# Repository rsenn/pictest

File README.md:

https://github.com/broedsels/PING2550
https://github.com/Apress/programming-pic-microcontrollers-w-xc8

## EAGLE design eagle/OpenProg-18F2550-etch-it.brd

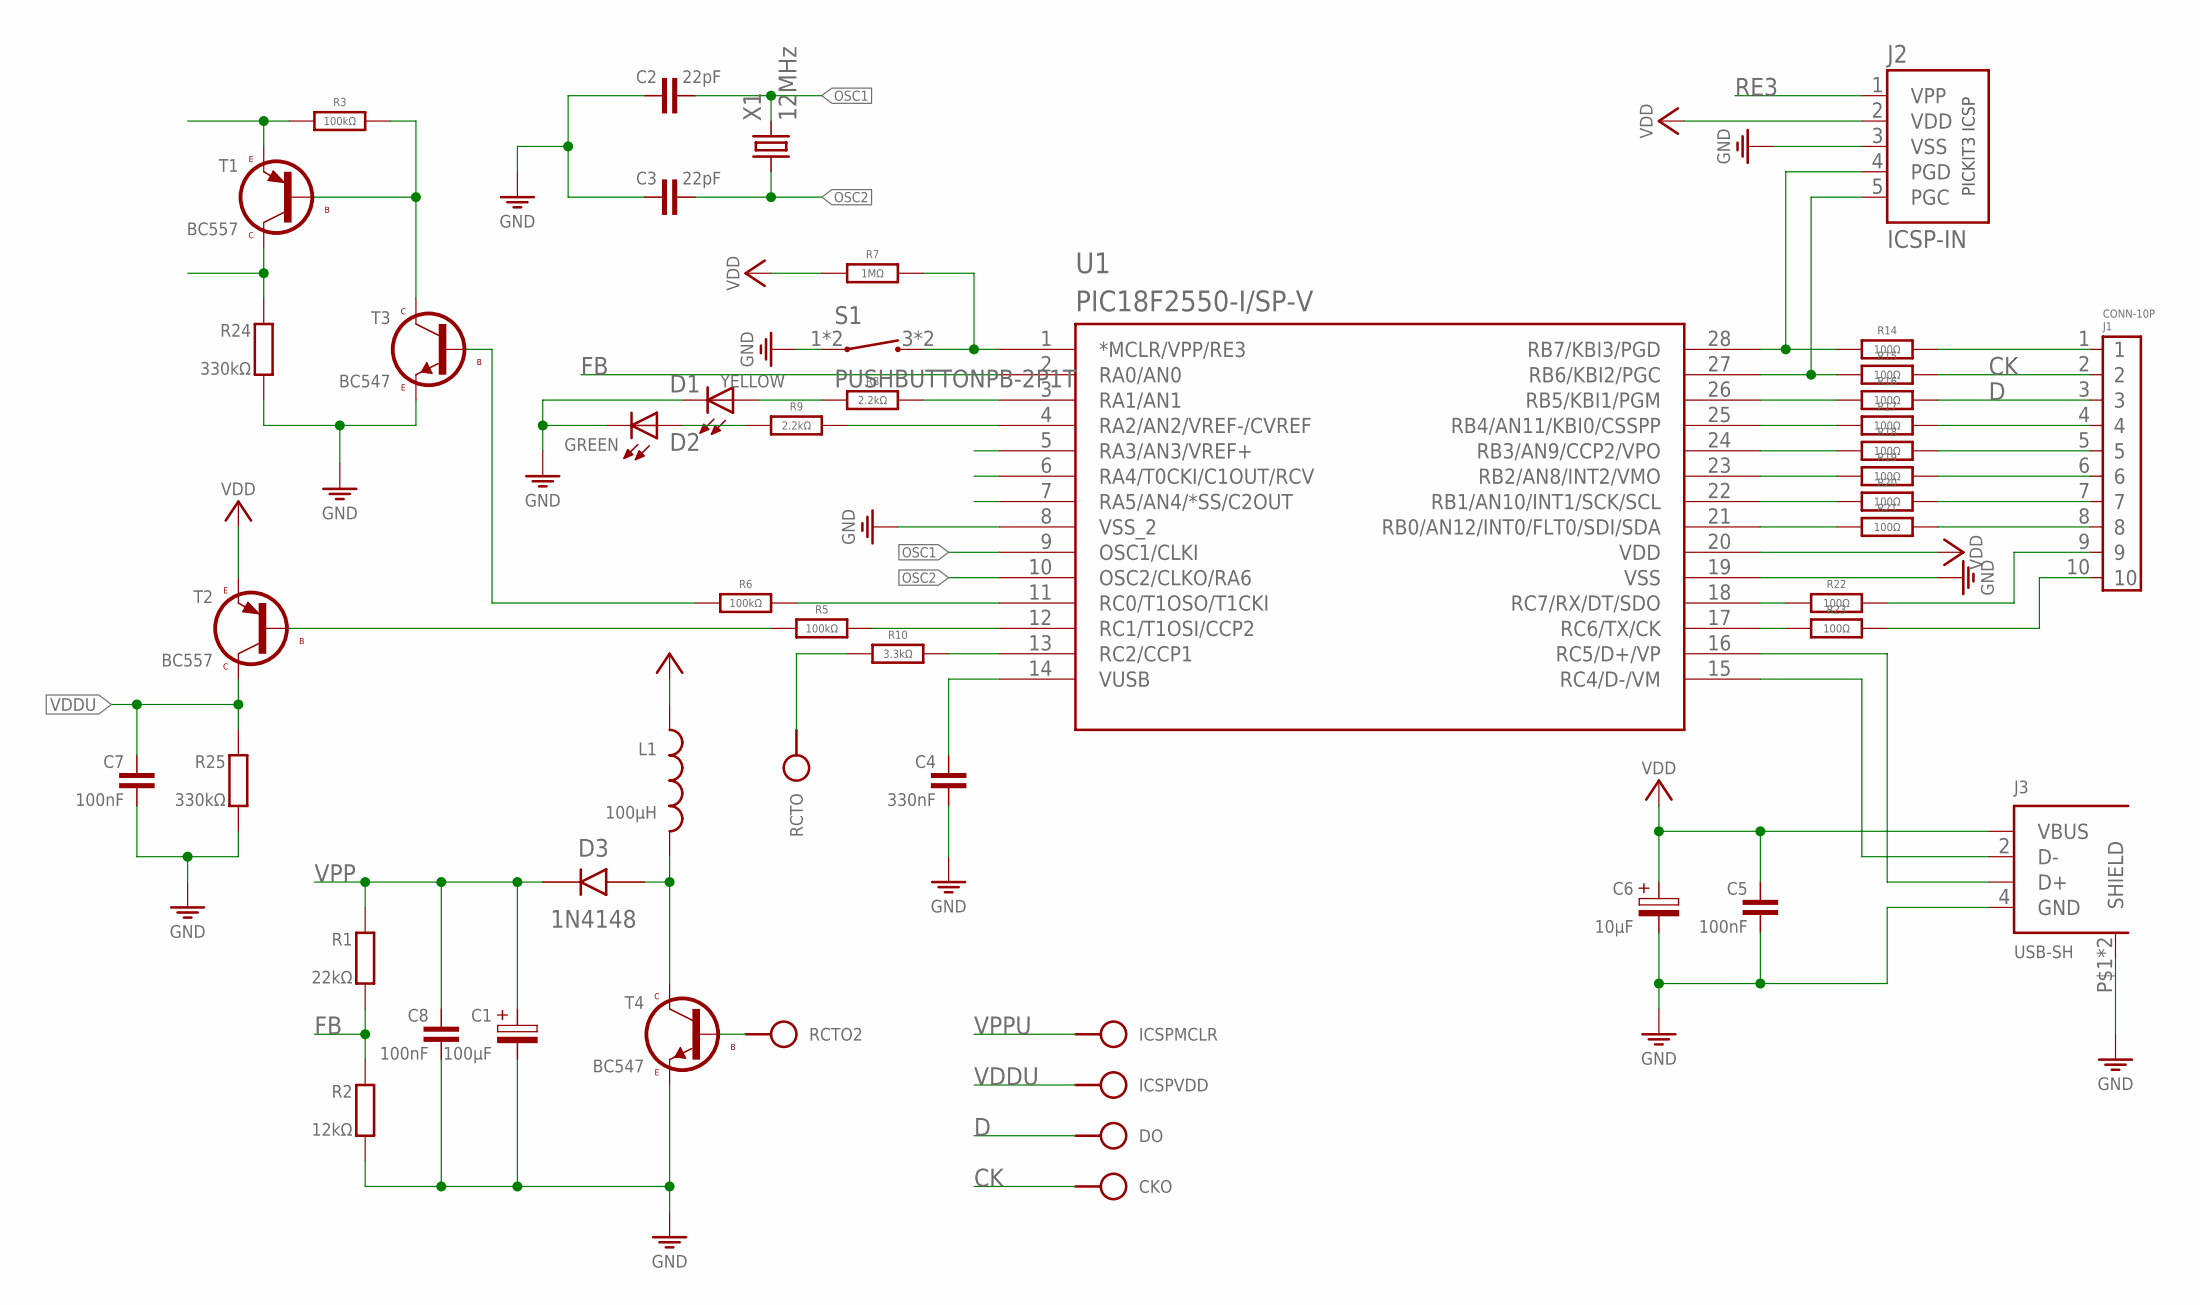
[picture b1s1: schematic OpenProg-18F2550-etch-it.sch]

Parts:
C1: 100μF; E2,5-5/V
C2, C3: 22pF; C025-015X024
C4: 330nF; C050-030X075
C5, C8: 100nF; C025-015X024
C6: 10μF; E2,5-5
C7: 100nF; C050-020X036
CKO: HPORT; SPAD
D1: YELLOW; LED_3MM
D2: GREEN; LED_3MM
D3: 1N4148; DO34-7
DO: HPORT; SPAD
ICSPMCLR: HPORT; SPAD
ICSPVDD: HPORT; SPAD
J1: CONN-10P
J2: ICSP-IN; PIC-PK3
J3: USB-SH; USB-B-PRINT
L1: 100µH; L-03/10V
R1: 22kΩ; 0204/10-V
R2: 12kΩ; 0204/10-V
R3: 100kΩ; 0204/2
R5, R6: 100kΩ; 0204/10
R7: 1MΩ; 0204/10-V
R8, R9: 2.2kΩ; 0204/10
R10: 3.3kΩ; 0204/10
R14, R15, R16, R17, R18, R19, R20, R21, R22, R23: 100Ω; 0204/10
R24, R25: 330kΩ; 0204/10-V
RCTO, RCTO2: HPORT; SPAD
S1: PUSHBUTTONPB-2P1T; PB-2P1T
T1, T2: BC557; TO92-CBE
T3, T4: BC547; TO92
U1: PIC18F2550-I/SP-V; DIL28-3/V
X1: 12MHz; HC49

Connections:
CK: CKO.1, J1.2, R15.2
D: DO.1, J1.3, R16.2
FB: R1.2 (1), R2.1 (2), U1.2 (RA0/AN0)
GND: C1.-, C2.1, C3.1, C4.2, C5.2, C6.-, C7.2, C8.2, D1.K (C), D2.K (C), J2.3 (VSS), J3.4 (GND), J3.P$1 (SHIELD), J3.P$2 (SHIELD), R2.2 (1), R24.2 (1), R25.2 (1), S1.1, S1.2 (1), T3.3 (E), T4.3 (E), U1.8 (VSS_2), U1.19 (VSS)
unnamed: R5.1, T2.2 (B)
unnamed: D3.A, L1.2, T4.1 (C)
unnamed: R10.1, RCTO.1
unnamed: R3.2, T1.2 (B), T3.1 (C)
unnamed: J2.4 (PGD), R14.1, U1.28 (RB7/KBI3/PGD)
unnamed: J2.5 (PGC), R15.1, U1.27 (RB6/KBI2/PGC)
unnamed: R16.1, U1.26 (RB5/KBI1/PGM)
unnamed: R17.1, U1.25 (RB4/AN11/KBI0/CSSPP)
unnamed: R18.1, U1.24 (RB3/AN9/CCP2/VPO)
unnamed: R19.1, U1.23 (RB2/AN8/INT2/VMO)
unnamed: R20.1, U1.22 (RB1/AN10/INT1/SCK/SCL)
unnamed: R21.1, U1.21 (RB0/AN12/INT0/FLT0/SDI/SDA)
unnamed: J1.1, R14.2
unnamed: J1.4, R17.2
unnamed: J1.5, R18.2
unnamed: J1.6, R19.2
unnamed: J1.7, R20.2
unnamed: R22.1, U1.18 (RC7/RX/DT/SDO)
unnamed: R23.1, U1.17 (RC6/TX/CK)
unnamed: J1.9, R22.2
unnamed: J1.10, R23.2
unnamed: J3.3 (D+), U1.16 (RC5/D+/VP)
unnamed: C4.1, U1.14 (VUSB)
unnamed: D1.A, R8.1
unnamed: D2.A, R9.1
OSC1: C2.2, U1.9 (OSC1/CLKI), X1.2
OSC2: C3.2, U1.10 (OSC2/CLKO/RA6), X1.1
RA1: R8.2, U1.3 (RA1/AN1)
RA2: R9.2, U1.4 (RA2/AN2/VREF-/CVREF)
RC0: R6.2, U1.11 (RC0/T1OSO/T1CKI)
RC1: R5.2, U1.12 (RC1/T1OSI/CCP2)
RC2: R10.2, U1.13 (RC2/CCP1)
RE3: J2.1 (VPP), R7.2, S1.3 (2), S1.4 (2), U1.1 (*MCLR/VPP/RE3)
VCC: C5.1, C6.+, J2.2 (VDD), J3.1 (VBUS), L1.1, R7.1, T2.3 (E), U1.20 (VDD)
VDD1: J1.8, R21.2
VDD3: J3.2 (D-), U1.15 (RC4/D-/VM)
VDDU: C7.1, ICSPVDD.1, R25.1 (2), T2.1 (C)
VPP: C1.+, C8.1, D3.C, R1.1 (2), R3.1, T1.3 (E)
VPPCTL: R6.1, T3.2 (B)
VPPU: ICSPMCLR.1, R24.1 (2), T1.1 (C)
VREGCTL: RCTO2.1, T4.2 (B)

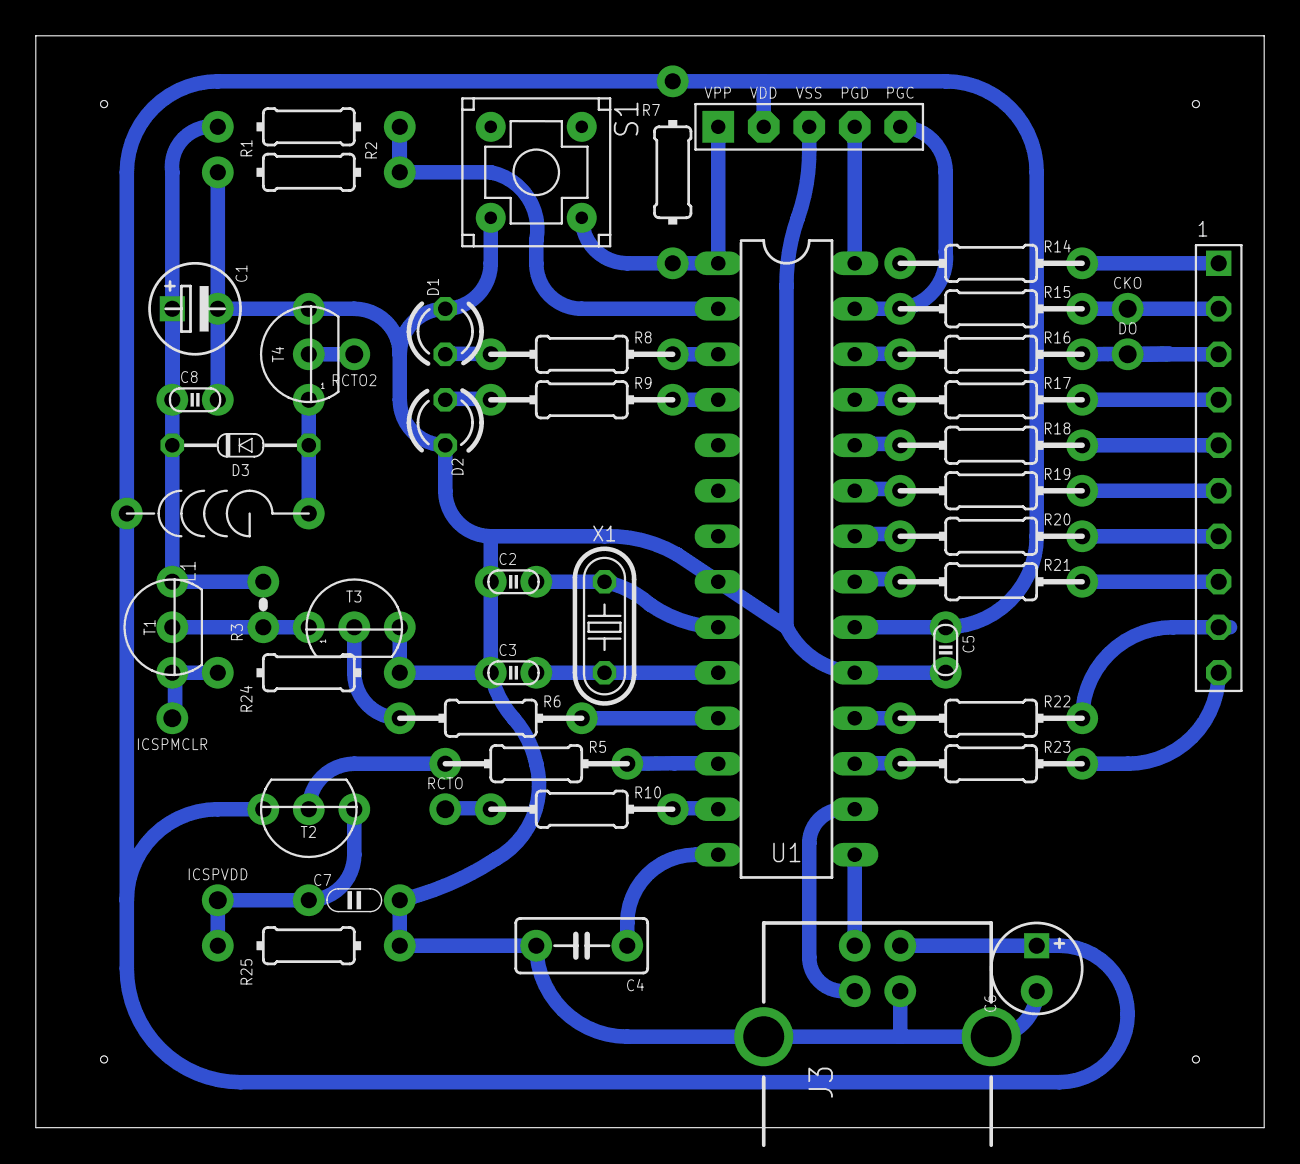
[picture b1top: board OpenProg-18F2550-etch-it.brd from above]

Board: 2 copper layers, 68.6 x 61.0 mm, 49 parts (0 on the bottom side), 45 nets.

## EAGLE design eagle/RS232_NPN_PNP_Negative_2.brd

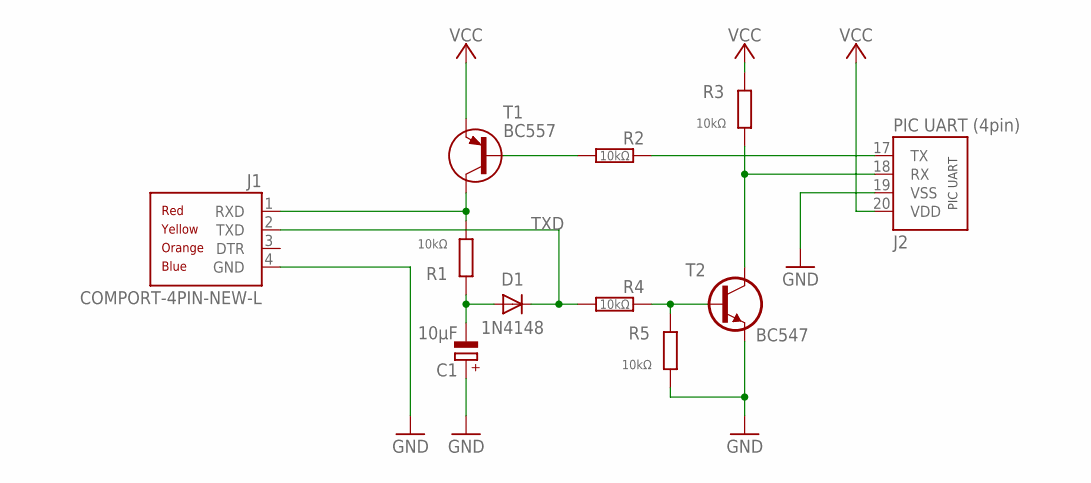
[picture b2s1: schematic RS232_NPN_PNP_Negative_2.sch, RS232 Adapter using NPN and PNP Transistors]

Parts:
C1: 10μF; E2,5-3/V
D1: 1N4148; DO34-5
J1: COMPORT-4PIN-NEW-L; RS232-4PIN-NEW-L
J2: PIC UART (4pin); PIC-UART
R1, R4, R5: 10kΩ; 0202/7
R2: 10kΩ; 0202/10-V
R3: 10kΩ; 0202/7-V
T1: BC557; TO92-CBE
T2: BC547; TO92-CBE

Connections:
-12V: C1.-, D1.A, R1.1
GND: C1.+, J1.4 (GND), J2.19 (VSS), R5.2, T2.E
unnamed: R2.2, T1.B
unnamed: R4.1, R5.1, T2.B
RX: J2.18 (RX), R3.1, T2.C
RXD: J1.1 (RXD), R1.2, T1.C
TX: J2.17 (TX), R2.1
TXD: D1.C, J1.2 (TXD), R4.2
VCC: J2.20 (VDD), R3.2, T1.E

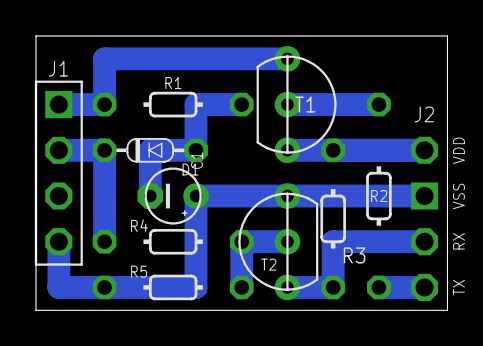
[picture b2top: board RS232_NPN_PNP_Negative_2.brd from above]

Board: 2 copper layers, 22.9 x 15.2 mm, 11 parts (0 on the bottom side), 9 nets.

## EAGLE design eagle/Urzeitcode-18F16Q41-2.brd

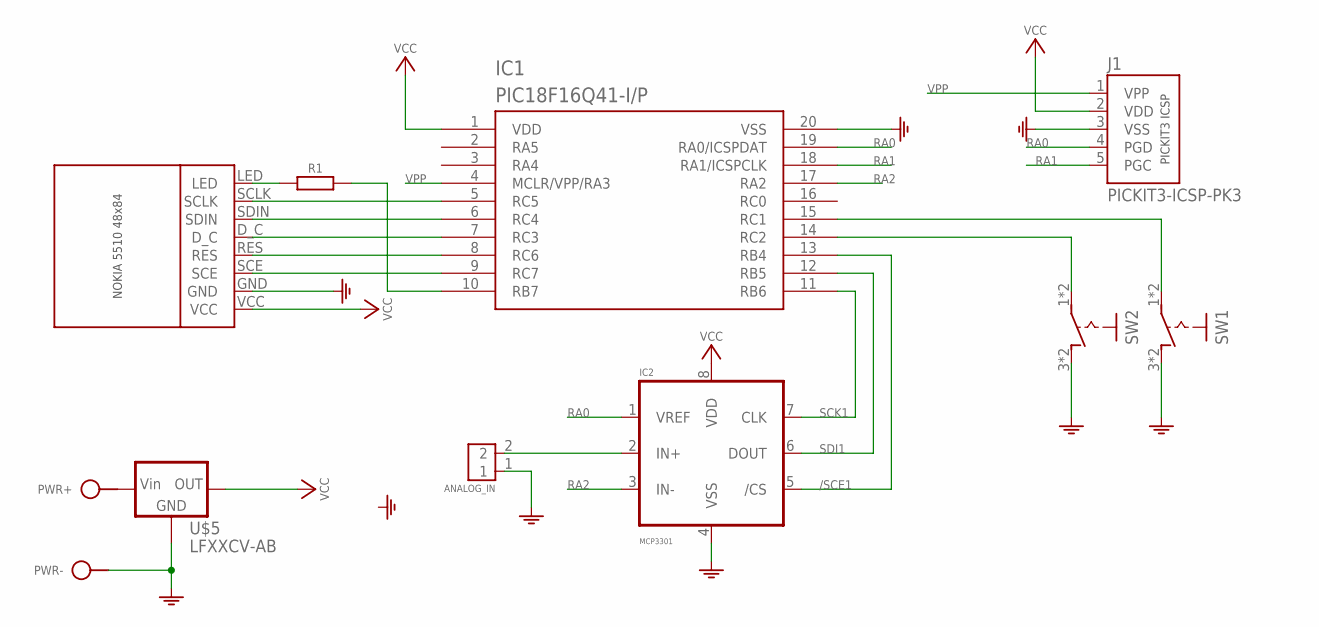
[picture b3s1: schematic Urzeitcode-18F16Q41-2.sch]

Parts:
ANALOG_IN: CONN-2P2P/H; CONN-2P
IC1: PIC18F16Q41-I/P; DIL20-3/V
IC2: MCP3301; DIL08
J1: PICKIT3-ICSP-PK3; PIC-PK3
PWR: SPAD+--+; SPAD-+
R1: R-H0204/15-V; 0204/15-V
SW1, SW2: PB-1P-1T2P1T; PB-2P1T
U$2: NOKIA-5510-48X84-MODULE; MOD-LCD5110
U$5: LFXXCV-AB; TO220AB

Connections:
/SCE1: IC1.13 (RB4), IC2.5 (/CS)
GND: ANALOG_IN.1, IC1.20 (VSS), IC2.4 (VSS), J1.3 (VSS), PWR.1, SW1.3 (S), SW1.4 (S), SW2.3 (S), SW2.4 (S), U$2.GND, U$5.2 (GND)
unnamed: PWR.2, U$5.1 (VIN)
unnamed: ANALOG_IN.2, IC2.2 (IN+)
unnamed: R1.1, U$2.LED
unnamed: IC1.14 (RC2), SW2.1, SW2.2
unnamed: IC1.15 (RC1), SW1.1, SW1.2
RA0: IC1.19 (RA0/ICSPDAT), IC2.1 (VREF), J1.4 (PGD)
RA1: IC1.18 (RA1/ICSPCLK), J1.5 (PGC)
RA2: IC1.17 (RA2), IC2.3 (IN-)
RB7: IC1.10 (RB7), R1.2
RC3: IC1.7 (RC3), U$2.D_C
RC4: IC1.6 (RC4), U$2.SDIN
RC5: IC1.5 (RC5), U$2.SCLK
RC6: IC1.8 (RC6), U$2.RES
RC7: IC1.9 (RC7), U$2.SCE
SCK1: IC1.11 (RB6), IC2.7 (CLK)
SDI1: IC1.12 (RB5), IC2.6 (DOUT)
VCC: IC1.1 (VDD), IC2.8 (VDD), J1.2 (VDD), U$2.VCC, U$5.3 (VOUT)
VPP: IC1.4 (MCLR/VPP/RA3), J1.1 (VPP)

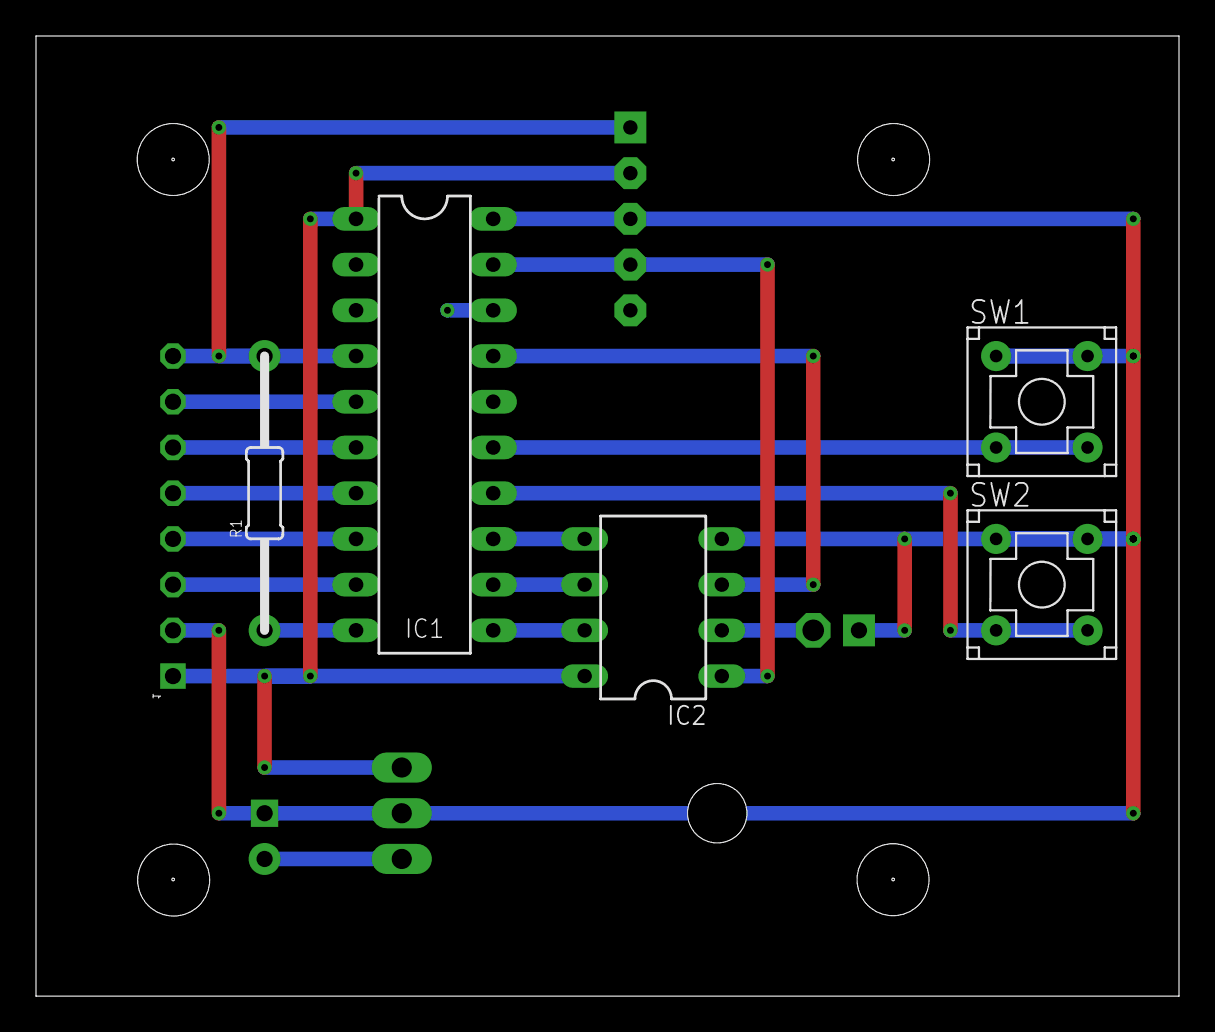
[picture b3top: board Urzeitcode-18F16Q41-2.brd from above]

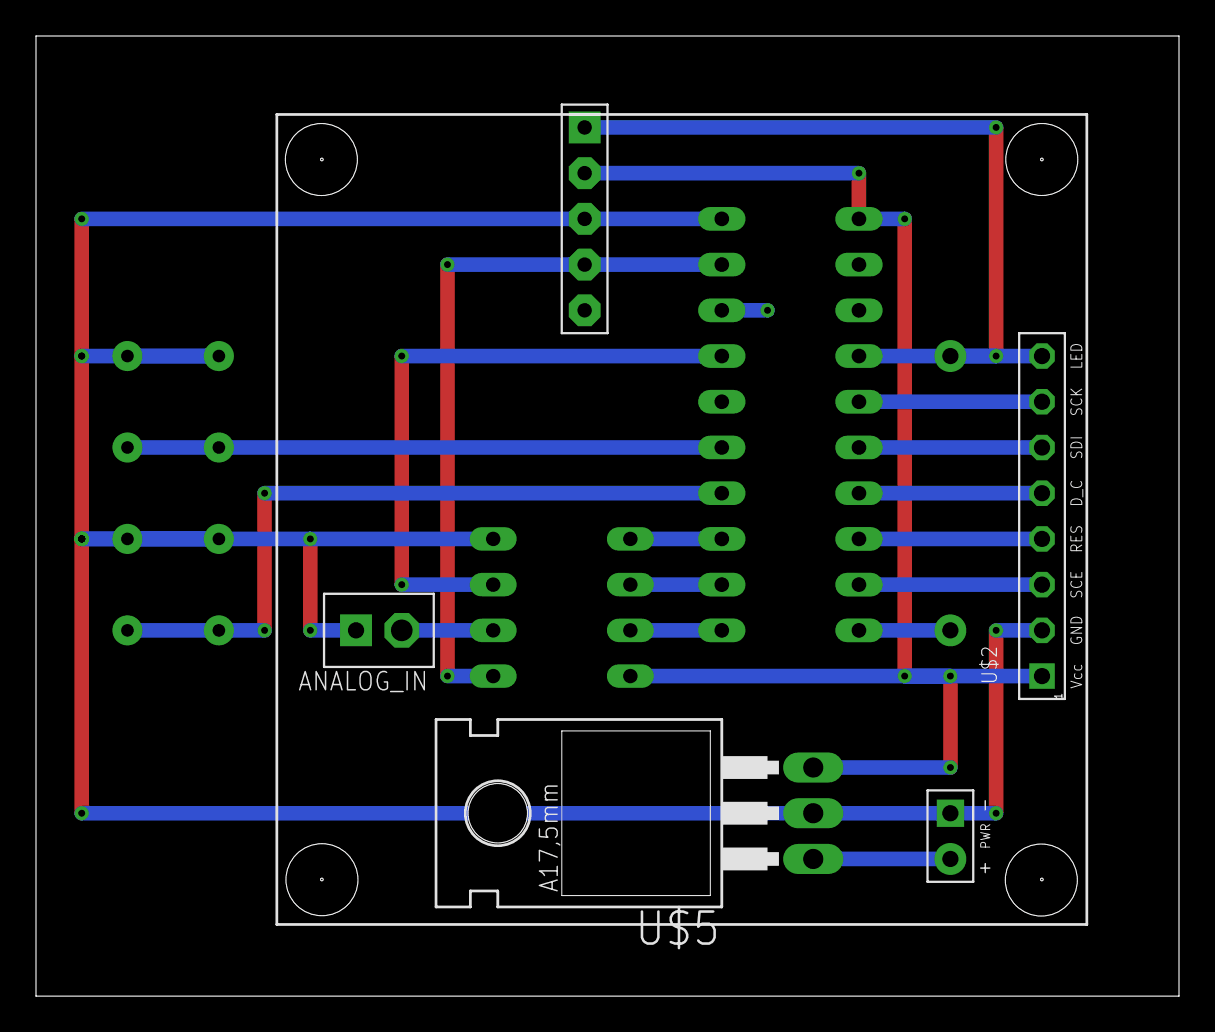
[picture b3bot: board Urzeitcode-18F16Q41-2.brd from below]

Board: 2 copper layers, 63.5 x 53.3 mm, 10 parts (4 on the bottom side), 20 nets.

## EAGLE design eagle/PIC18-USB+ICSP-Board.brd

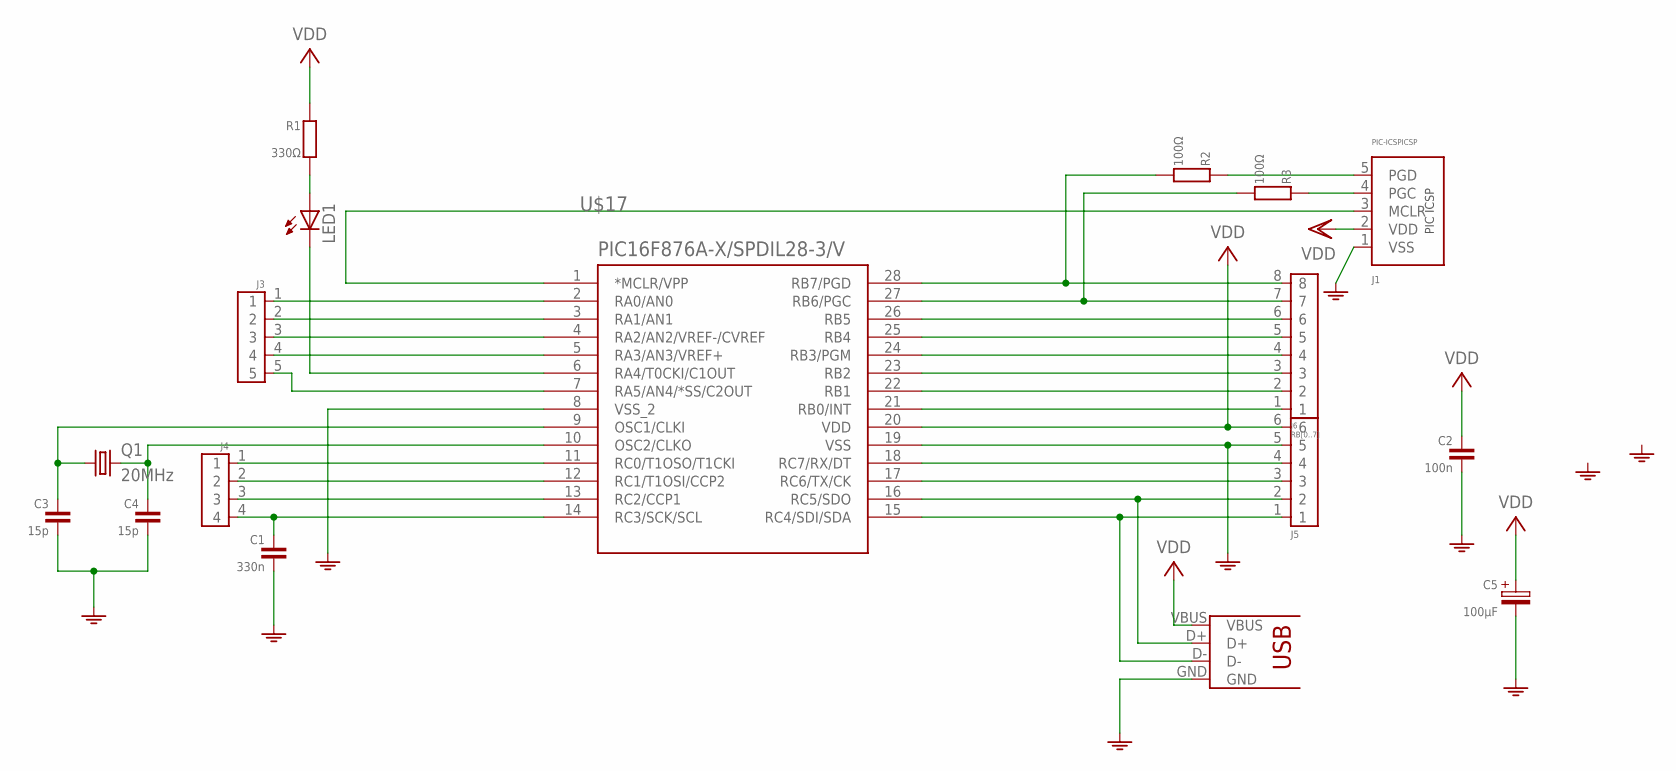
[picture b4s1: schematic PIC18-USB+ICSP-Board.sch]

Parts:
C1: 330n; C050-030X075
C2: 100n; C025-015X024
C3, C4: 15p; C025-015X024
C5: 100μF; E2,5-5
J1: PIC-ICSPICSP; PIC-ICSP
J2: USB-PRINT; USB-B-PRINT
J3: RA[0..4]; CONN-5P
J4: RC[0..3]; CONN-4P
J5: PWR+SCI+USB; CONN-6P
J6: RB[0..7]; CONN-8P
LED1: LED5MM
Q1: 20MHz; HC49
R1: 330Ω; 0204/10
R2, R3: 100Ω; 0204/7-V
U$17: PIC16F876A-X/SPDIL28-3/V; DIL28-3/V

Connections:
/MCLR: J1.3 (MCLR), U$17.1 (*MCLR/VPP)
GND: C1.2, C2.2, C3.2, C4.2, C5.-, J1.1 (VSS), J2.GND, J5.5, U$17.8 (VSS_2), U$17.19 (VSS)
unnamed: C1.1, J4.4, U$17.14 (RC3/SCK/SCL)
unnamed: J2.D+, J5.2, U$17.16 (RC5/SDO)
unnamed: J2.D-, J5.1, U$17.15 (RC4/SDI/SDA)
unnamed: LED1.A, R1.2 (1)
unnamed: J3.5, U$17.7 (RA5/AN4/*SS/C2OUT)
unnamed: C3.1, Q1.1, U$17.9 (OSC1/CLKI)
unnamed: C4.1, Q1.2, U$17.10 (OSC2/CLKO)
unnamed: J6.6, U$17.26 (RB5)
unnamed: J6.5, U$17.25 (RB4)
unnamed: J6.4, U$17.24 (RB3/PGM)
unnamed: J6.3, U$17.23 (RB2)
unnamed: J6.2, U$17.22 (RB1)
unnamed: J6.1, U$17.21 (RB0/INT)
unnamed: J3.1, U$17.2 (RA0/AN0)
unnamed: J5.4, U$17.18 (RC7/RX/DT)
unnamed: J5.3, U$17.17 (RC6/TX/CK)
unnamed: J3.2, U$17.3 (RA1/AN1)
unnamed: J3.3, U$17.4 (RA2/AN2/VREF-/CVREF)
unnamed: J3.4, U$17.5 (RA3/AN3/VREF+)
unnamed: LED1.K (C), U$17.6 (RA4/T0CKI/C1OUT)
unnamed: J4.1, U$17.11 (RC0/T1OSO/T1CKI)
unnamed: J4.2, U$17.12 (RC1/T1OSI/CCP2)
unnamed: J4.3, U$17.13 (RC2/CCP1)
unnamed: J1.5 (PGD), R2.1 (2)
unnamed: J1.4 (PGC), R3.1 (2)
PGC: J6.7, R3.2 (1), U$17.27 (RB6/PGC)
PGD: J6.8, R2.2 (1), U$17.28 (RB7/PGD)
VDD: C2.1, C5.+, J1.2 (VDD), J2.VBUS, J5.6, R1.1 (2), U$17.20 (VDD)

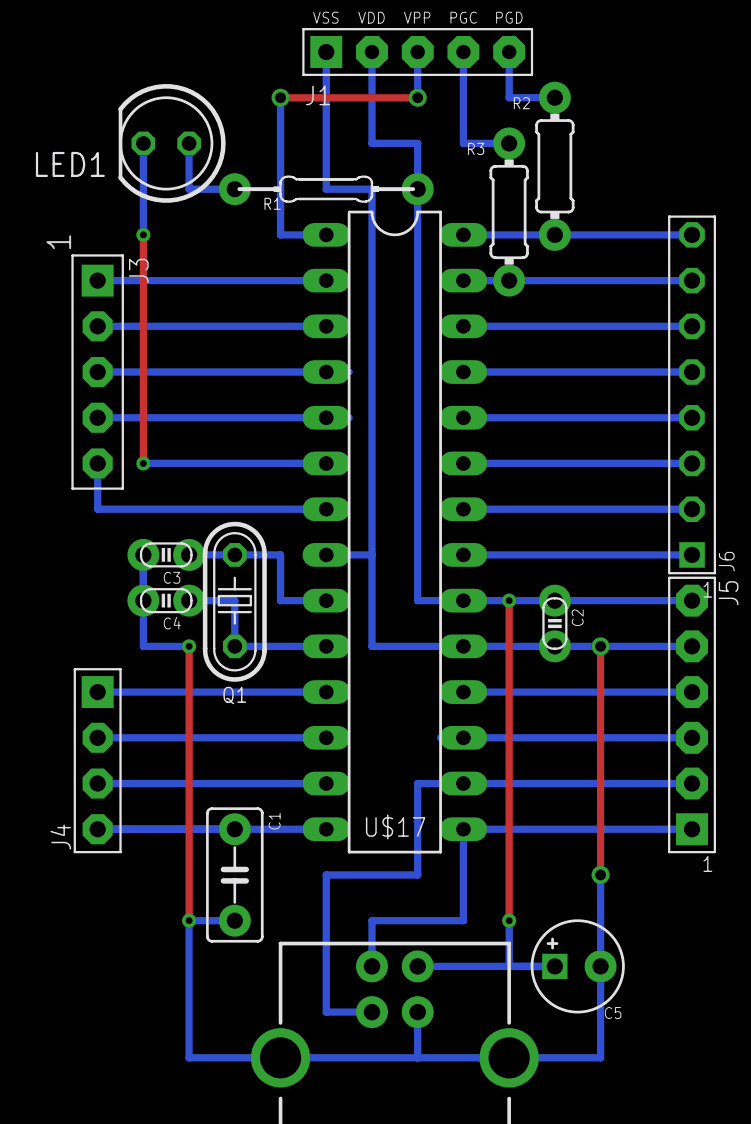
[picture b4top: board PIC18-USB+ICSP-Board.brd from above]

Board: 2 copper layers, 17 parts (0 on the bottom side), 30 nets.

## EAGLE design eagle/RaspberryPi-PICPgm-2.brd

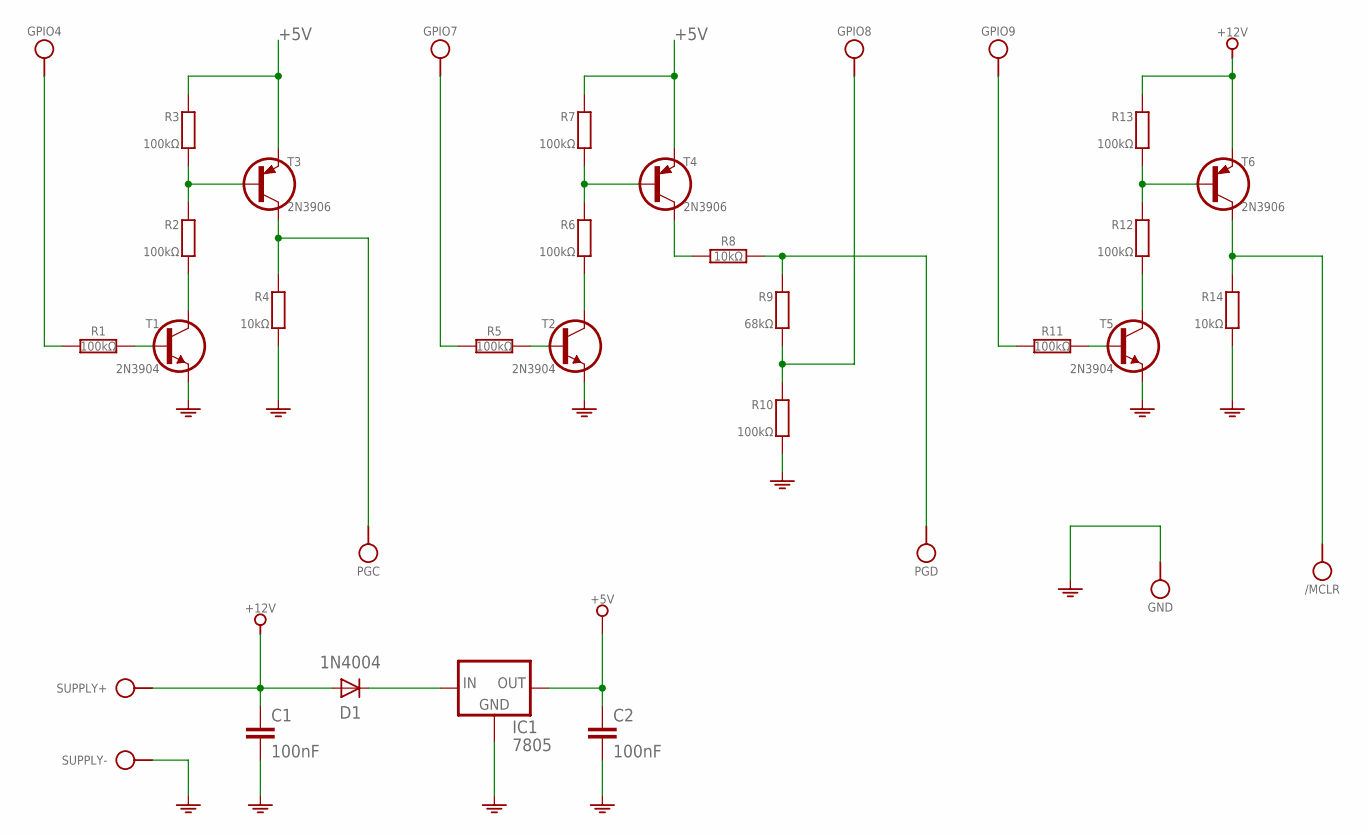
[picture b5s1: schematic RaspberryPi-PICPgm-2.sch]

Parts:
/MCLR: VPORT; SPAD
C1, C2: 100nF; C050-025X075
D1: 1N4004; DO41-10
GND: VPORT; SPAD
GPIO4, GPIO7, GPIO8, GPIO9: VPORT; SPAD
IC1: 7805; TO220
PGC: VPORT; SPAD
PGD: VPORT; SPAD
R1, R5, R11: 100kΩ; 0204/10
R2, R3, R6, R7, R10, R12, R13: 100kΩ; 0204/10-V
R4, R14: 10kΩ; 0204/10-V
R8: 10kΩ; 0204/10
R9: 68kΩ; 0204/10-V
SUPPLY: SPAD+--+; SPAD-+
T1, T2, T5: 2N3904; TO92-EBC
T3, T4, T6: 2N3906; TO92-EBC

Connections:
+5V: C2.1, IC1.3 (OUT), R3.1 (2), R7.1 (2), T3.E, T4.E
+12V: C1.1, D1.A, R13.1 (2), SUPPLY.2, T6.E
GND: C1.2, C2.2, GND.1, IC1.2 (GND), R4.2 (1), R10.2 (1), R14.2 (1), SUPPLY.1, T1.E, T2.E, T5.E
unnamed: GPIO4.1, R1.1
unnamed: R1.2, T1.B
unnamed: R2.2 (1), T1.C
unnamed: R2.1 (2), R3.2 (1), T3.B
unnamed: PGC.1, R4.1 (2), T3.C
unnamed: GPIO7.1, R5.1
unnamed: R5.2, T2.B
unnamed: R6.2 (1), T2.C
unnamed: R6.1 (2), R7.2 (1), T4.B
unnamed: R8.1, T4.C
unnamed: PGD.1, R8.2, R9.1 (2)
unnamed: GPIO8.1, R9.2 (1), R10.1 (2)
unnamed: GPIO9.1, R11.1
unnamed: R11.2, T5.B
unnamed: R12.2 (1), T5.C
unnamed: R12.1 (2), R13.2 (1), T6.B
unnamed: /MCLR.1, R14.1 (2), T6.C
unnamed: D1.C, IC1.1 (IN)

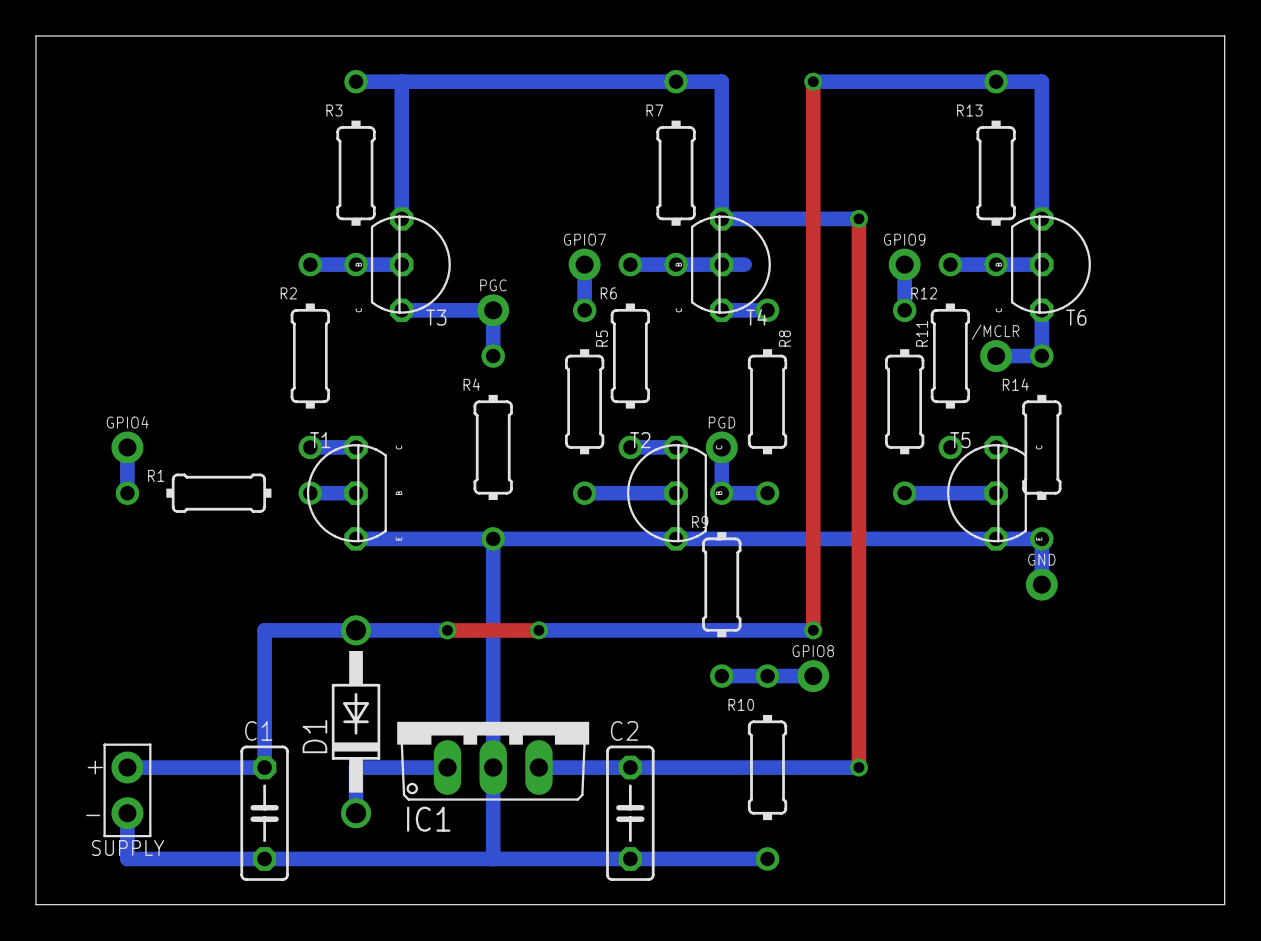
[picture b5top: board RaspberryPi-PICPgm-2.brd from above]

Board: 2 copper layers, 66.0 x 48.3 mm, 33 parts (0 on the bottom side), 21 nets.

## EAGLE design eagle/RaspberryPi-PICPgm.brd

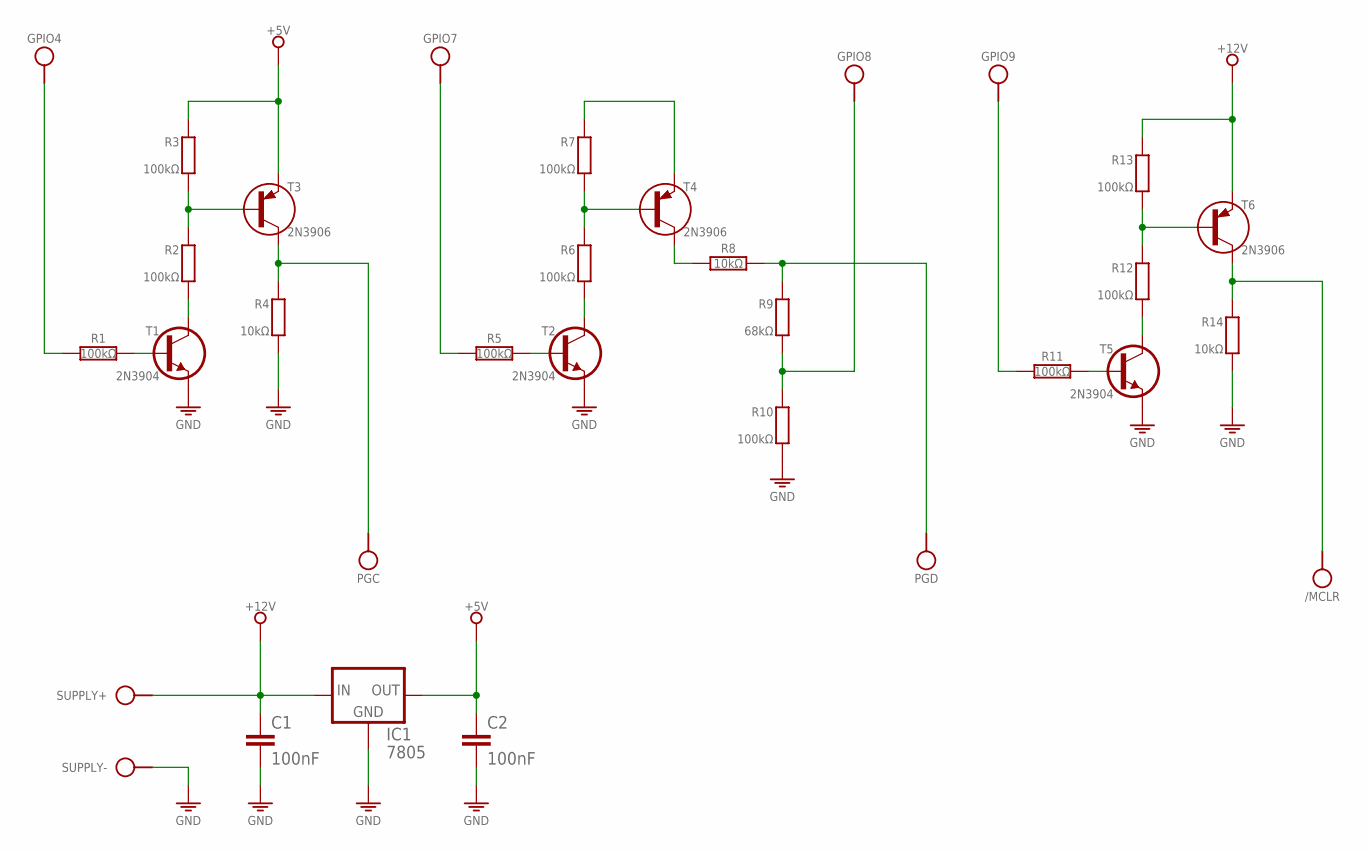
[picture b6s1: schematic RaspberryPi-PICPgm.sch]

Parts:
/MCLR: VPORT; SPAD
C1, C2: 100nF; C050-025X075
GPIO4, GPIO7, GPIO8, GPIO9: VPORT; SPAD
IC1: 7805; TO220
PGC: VPORT; SPAD
PGD: VPORT; SPAD
R1, R5, R11: 100kΩ; 0204/10
R2, R3, R6, R7, R10, R12, R13: 100kΩ; 0204/10-V
R4, R14: 10kΩ; 0204/10-V
R8: 10kΩ; 0204/10
R9: 68kΩ; 0204/10-V
SUPPLY: SPAD+--+; SPAD-+
T1, T2, T5: 2N3904; TO92
T3, T4, T6: 2N3906; TO92

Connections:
+5V: C2.1, IC1.3 (OUT), R3.1 (2), R7.1 (2), T3.1 (E), T4.1 (E)
+12V: C1.1, IC1.1 (IN), R13.1 (2), SUPPLY.2, T6.1 (E)
/MCLR: /MCLR.1, R14.1 (2), T6.3 (C)
GND: C1.2, C2.2, IC1.2 (GND), R4.2 (1), R10.2 (1), R14.2 (1), SUPPLY.1, T1.1 (E), T2.1 (E), T5.1 (E)
GPIO4: GPIO4.1, R1.1
GPIO7: GPIO7.1, R5.1
GPIO8: GPIO8.1, R9.2 (1), R10.1 (2)
GPIO9: GPIO9.1, R11.1
unnamed: R1.2, T1.2 (B)
unnamed: R2.2 (1), T1.3 (C)
unnamed: R2.1 (2), R3.2 (1), T3.2 (B)
unnamed: R5.2, T2.2 (B)
unnamed: R6.2 (1), T2.3 (C)
unnamed: R6.1 (2), R7.2 (1), T4.2 (B)
unnamed: R8.1, T4.3 (C)
unnamed: R11.2, T5.2 (B)
unnamed: R12.2 (1), T5.3 (C)
unnamed: R12.1 (2), R13.2 (1), T6.2 (B)
PGC: PGC.1, R4.1 (2), T3.3 (C)
PGD: PGD.1, R8.2, R9.1 (2)

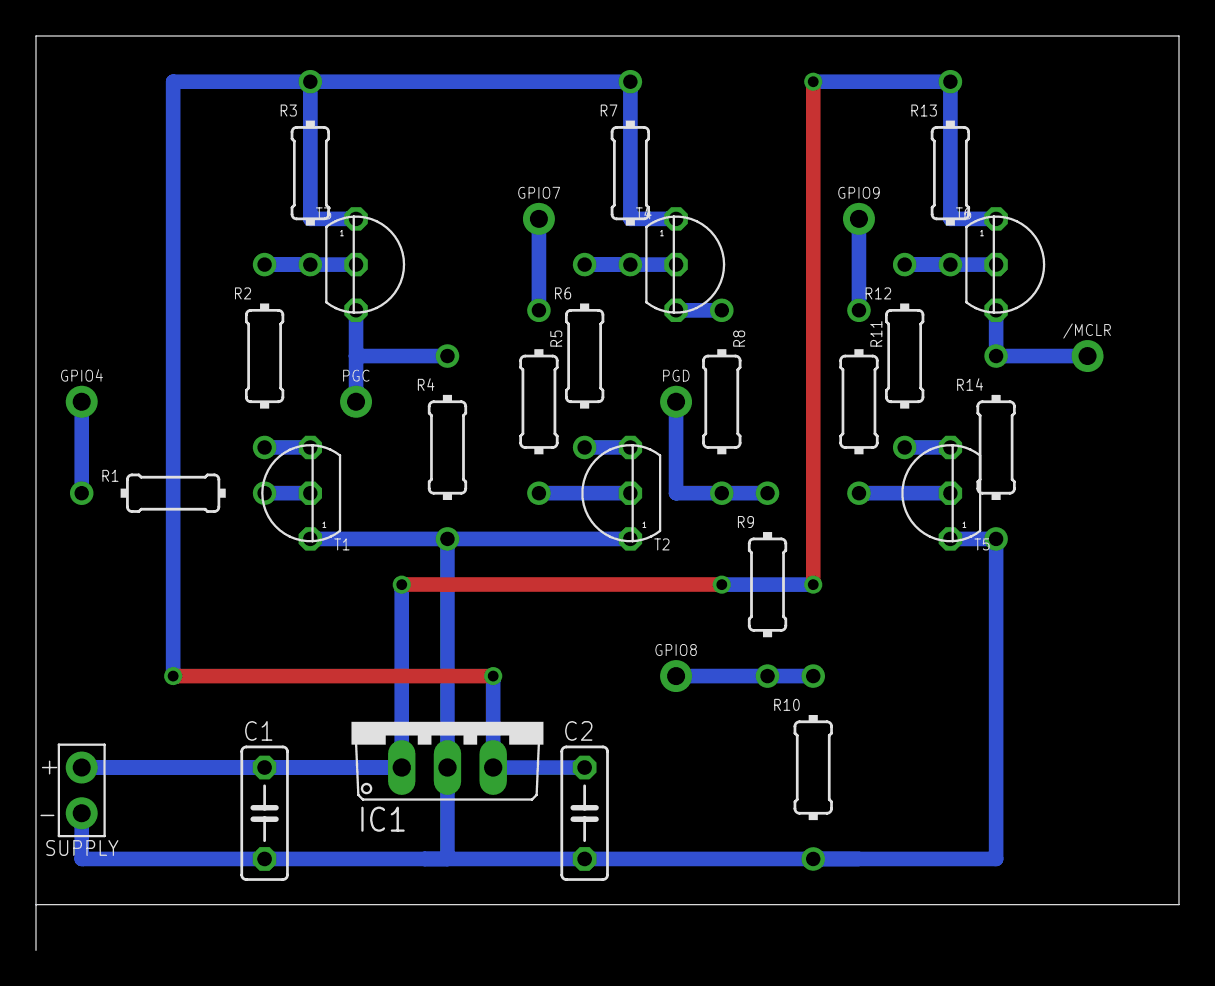
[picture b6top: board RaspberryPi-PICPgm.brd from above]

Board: 2 copper layers, 63.5 x 50.8 mm, 31 parts (0 on the bottom side), 20 nets.

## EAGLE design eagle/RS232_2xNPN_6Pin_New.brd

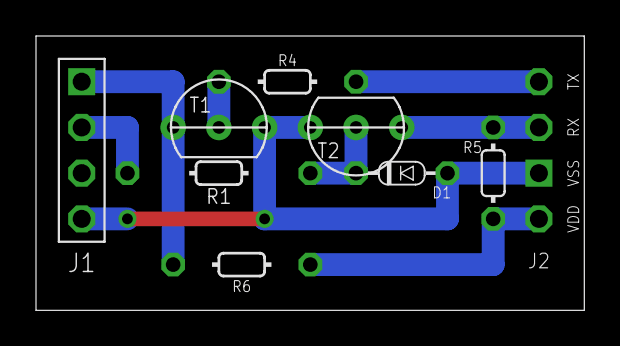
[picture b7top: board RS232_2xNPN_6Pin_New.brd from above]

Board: 2 copper layers, 30.5 x 15.2 mm, 9 parts (0 on the bottom side), 8 nets.

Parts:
D1: 1N4148; DO34-5
J1: COMPORT-4PIN-NEW-L; RS232-4PIN-NEW-L
J2: PIC-UART-X
R1: 4.7kΩ; 0202/10
R4: 10kΩ; 0202/7
R5: 1kΩ; 0202/5-V
R6: 1kΩ; 0202/7
T1, T2: BC547; TO92-CBE

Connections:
+5V: J2.20, R5.2, R6.2
GND: D1.A, J1.4, J2.19, T1.E, T2.E
unnamed: J2.18, R5.1, T2.C
unnamed: D1.C, R1.1, T2.B
unnamed: J2.17, R4.1
unnamed: R4.2, T1.B
RXD: J1.1, R6.1, T1.C
TXD: J1.2, R1.2

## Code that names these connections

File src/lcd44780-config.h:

#ifdef __16f628a
#define RS_PIN RB5
#define RS_TRIS TRISB5
#undef RW_PIN
#undef RW_TRIS
#define EN_PIN RB4
#define EN_TRIS TRISB4

#define DATA0_PIN RA2
#define DATA0_TRIS TRISA2
#define DATA1_PIN RA3
#define DATA1_TRIS TRISA3
#define DATA2_PIN RB3
#define DATA2_TRIS TRISB3
#define DATA3_PIN RB6
#define DATA3_TRIS TRISB6
#else
#define RS_PIN RB2
#define RS_TRIS TRISB2
#undef RW_PIN
#undef RW_TRIS
#define EN_PIN RB3     // activated by a HIGH pulse.
#define EN_TRIS TRISB3 // activated by a HIGH pulse.

#define DATA0_PIN RB4
#define DATA0_TRIS TRISB4
#define DATA1_PIN RB5
#define DATA1_TRIS TRISB5
#define DATA2_PIN RB6
#define DATA2_TRIS TRISB6
#define DATA3_PIN RB7
#define DATA3_TRIS TRISB7
#endif

#ifndef DATABUS_MUX
#define DATABUS_MUX 0
#endif

#if DATABUS_MUX
#define DATABUS_INIT INPUT
#define DATABUS_MUXDELAY 10
#else
#define DATABUS_INIT OUTPUT
#endif

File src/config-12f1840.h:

#ifndef CONFIG_12F1840_H
#define CONFIG_12F1840_H 1

#if defined(__XC) || defined(MCHP_XC8) || defined(__XC__) || defined(XC8)

// Word CONFIG1 @ 0x8007
#pragma config FOSC = INTOSC
#pragma config WDTE = OFF     // Watchdog Timer Enable [ NSLEEP | OFF | ON | SWDTEN ]
#pragma config PWRTE = ON     // Power-up Timer Enable [ OFF | ON   ]
#pragma config MCLRE = OFF    // MCLR Pin Function Select [ OFF | ON   ]
#pragma config CP = OFF       // Flash Program Memory Code Protection [ OFF | ON   ]
#pragma config CPD = OFF      // Data Memory Code Protection [ OFF | ON   ]
#pragma config BOREN = ON     // Brown-out Reset Enable [ NSLEEP | OFF | ON | SBODEN ]
#pragma config CLKOUTEN = OFF // Clock Out Enable [ OFF | ON   ]
#pragma config IESO = OFF     // Internal/External Switchover [ OFF | ON   ]

// Word CONFIG2 @ 0x8008

#pragma config FCMEN = OFF // Fail-Safe Clock Monitor Enable [ OFF | ON   ]
#pragma config WRT = OFF   // Flash Memory Self-Write Protection [ ALL | BOOT | HALF | OFF ]
#pragma config PLLEN = ON  // PLL Enable [ OFF | ON   ]
#pragma config STVREN = ON // Stack Overflow/Underflow Reset Enable [ OFF | ON   ]
#pragma config BORV = LO   // Brown-out Reset Voltage Selection [ HI | LO    ]

#elif defined(__SDCC__) || defined(SDCC)
#define _CONFIG1 0x8007

#define _FOSC_LP 0x3FF8      // LP Oscillator, Low-power crystal connected between OSC1 and OSC2 pins.
#define _FOSC_XT 0x3FF9      // XT Oscillator, Crystal/resonator connected between OSC1 and OSC2 pins.
#define _FOSC_HS 0x3FFA      // HS Oscillator, High-speed crystal/resonator connected between OSC1 and OSC2 pins.
#define _FOSC_EXTRC 0x3FFB   // EXTRC oscillator: External RC circuit connected to CLKIN pin.
#define _FOSC_INTOSC 0x3FFC  // INTOSC oscillator: I/O function on CLKIN pin.
#define _FOSC_ECL 0x3FFD     // ECL, External Clock, Low Power Mode (0-0.5 MHz): device clock supplied to CLKIN pin.
#define _FOSC_ECM 0x3FFE     // ECM, External Clock, Medium Power Mode (0.5-4 MHz): device clock supplied to CLKIN pin.
#define _FOSC_ECH 0x3FFF     // ECH, External Clock, High Power Mode (4-32 MHz): device clock supplied to CLKIN pin.
#define _WDTE_OFF 0x3FE7     // WDT disabled.
#define _WDTE_SWDTEN 0x3FEF  // WDT controlled by the SWDTEN bit in the WDTCON register.
#define _WDTE_NSLEEP 0x3FF7  // WDT enabled while running and disabled in Sleep.
#define _WDTE_ON 0x3FFF      // WDT enabled.
#define _PWRTE_ON 0x3FDF     // PWRT enabled.
#define _PWRTE_OFF 0x3FFF    // PWRT disabled.
#define _MCLRE_OFF 0x3FBF    // MCLR/VPP pin function is digital input.
#define _MCLRE_ON 0x3FFF     // MCLR/VPP pin function is MCLR.
#define _CP_ON 0x3F7F        // Program memory code protection is enabled.
#define _CP_OFF 0x3FFF       // Program memory code protection is disabled.
#define _CPD_ON 0x3EFF       // Data memory code protection is enabled.
#define _CPD_OFF 0x3FFF      // Data memory code protection is disabled.
#define _BOREN_OFF 0x39FF    // Brown-out Reset disabled.
#define _BOREN_SBODEN 0x3BFF // Brown-out Reset controlled by the SBOREN bit in the BORCON register.
#define _BOREN_NSLEEP 0x3DFF // Brown-out Reset enabled while running and disabled in Sleep.
#define _BOREN_ON 0x3FFF     // Brown-out Reset enabled.
#define _CLKOUTEN_ON 0x37FF  // CLKOUT function is enabled on the CLKOUT pin.
#define _CLKOUTEN_OFF 0x3FFF // CLKOUT function is disabled. I/O or oscillator function on the CLKOUT pin.
#define _IESO_OFF 0x2FFF     // Internal/External Switchover mode is disabled.
#define _IESO_ON 0x3FFF      // Internal/External Switchover mode is enabled.
#define _FCMEN_OFF 0x1FFF    // Fail-Safe Clock Monitor is disabled.
#define _FCMEN_ON 0x3FFF     // Fail-Safe Clock Monitor is enabled.

static __code char __at(_CONFIG1) configword1 = 0x3fff; //_FOSC_INTOSC & _WDTE_OFF & _PWRTE_ON & _MCLRE_OFF & _CP_OFF &
                                                        //_CPD_OFF & _BOREN_ON & _CLKOUTEN_OFF & _IESO_OFF & _FCMEN_OFF;
static __code char __at(_CONFIG2) configword2 = 0x3fff; //_FOSC_INTOSC & _WDTE_OFF & _PWRTE_ON & _MCLRE_OFF & _CP_OFF &
                                                        //_CPD_OFF & _BOREN_ON & _CLKOUTEN_OFF & _IESO_OFF & _FCMEN_OFF;

#pragma config FOSC = INTOSC, WDTE = OFF, PWRTE = ON, MCLRE = OFF, CP = OFF, CPD = OFF, BOREN = ON, CLKOUTEN = OFF,    \
               IESO = OFF, FCMEN = OFF, WRT = OFF, PLLEN = ON, STVREN = ON, BORV = LO, LVP = OFF

#elif defined(HI_TECH_C)

__CONFIG(1, FOSC_INTOSC& WDTE_OFF& PWRTE_ON& MCLRE_OFF& BOREN_ON& CP_OFF& CPD_OFF& CLKOUTEN_OFF);
__CONFIG(2, BORV_LO& WRT_OFF);

#endif

#endif // defined CONFIG_12F1840_H
